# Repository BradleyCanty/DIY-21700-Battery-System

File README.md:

# DIY-21700-Battery-System
## Introduction
This is a do-it-yourself battery system intended for use with Unmanned Aerial Vehicles or Unmanned Ground Vehicles.

It consists of...

1) a battery using lithium ion 21700-form-factor cells, with battery configurations spanning from 6s3p to 12s6p
2) a vehicle adapter with place-to-lock/press-to-unlock latching mechanism
3) an off-vehicle charging station

(12s4p battery system configuration shown below)

**This is a complete and working system, with all design files (CAD and PCB design) provided for your use:**\
Multiple battery system configurations have been built and flight tested. Additionally, all CAD models have been 3D printed to ensure they work as intended. Finally, if none of the configurations presented here suit your needs then you can create your own battery configuration, since all CAD files (Solidworks part files and STLs) and PCB design files (KiCad project files) are included here for your use.

**Version 2 will have cell voltage and temperature monitoring safety features (sent as a BATTERY_STATUS message over MAVLink to MAVLink-compatible autopilot software, such as ArduPilot and PX4) so star this repo for updates**

## Purpose
The parametric nature of this system allows designing and building a battery system specific to your vehicle's requirements. As such, **the value add of this system is threefold:**
1) you can use cells of your choice (i.e., can optimize for either power output or energy capacity) in a configuration suitable for your vehicle's operating envelope
2) you can enjoy a significant cost savings (~50% discount at the time of this writing) by building it yourself (see 'Bill of Materials' section for cost info)
3) the battery's latching mechanism presents a common interface for battery swapping (either manually or by robot arm); this is important since battery swapping vastly increases system uptime when compared with on-board charging

## Battery Mounting Choice
This battery system is designed such that the battery itself is top-mounted onto the vehicle its powering (and top-mounted onto its charging station). This mounting method was chosen to simplify battery swapping (either by human hand or by robot gripper); the process to swap the battery is as follows:
1. get within close proximity of the battery
2. translate grippers directly over the battery
3. rotate grippers to be aligned with the battery end plates
4. translate grippers underneath each end plate ledge
5. close grippers such that the end plate buttons are pressed down, thus unlatching the battery from the vehicle adapter
6. lift battery away from the vehicle
7. carry battery to its charging station

A similar but reversed process occurs for taking a fully charged battery off its charging station to the vehicle.

If you intend for such a battery to power your multirotor you might ask: "wouldn't the multirotor be top heavy, thereby adversely affecting stability and control?". The simple answer is no, it wouldn't **if you mount the battery directly above the bulkhead where the motor arms are mounted to the body**. In doing this, the center of gravity moves closer to the thrust plane (i.e. the plane where the rotors spin), which decreases overall inertia and thereby increases control responsiveness. So the overall impact is positive, not adverse. As final proof of functionality, I have personally flight tested a multirotor using a 12s4p battery, with no stability or control issues whatsoever.

(12s4p battery and vehicle adapter used on large quadcopter shown below)

Details on mounting the vehicle adapter to the vehicle can be found in Build Step 7: [Integrate vehicle adapter into vehicle](5_Integration_and_Test_Instructions/1_Vehicle_Adapter_Integration_Instructions/vehicle_adapter_integration_instructions.md)

## Cell Form Factor Choice
Considering the cell form factor, **21700 cells** (i.e. cylindrical cells having 21[mm] height and 70[mm] length) **are used in the battery since they are cheap, easily obtained, and have high gravimetric energy density**. In comparison to other cells types, 18650 cells tend to have lower gravimetric energy density, while 4680 cells, prismatic cells, and pouch cells aren't widely available to the general public (as of late 2026). Concerning battery design, the battery configuration is defined by its number of cells in series (which sets its voltage) and its number of cells in parallel (which sets its charge capacity and its max current draw limit). In the system presented here, the possible number of cells in series ranges from 6 to 12, while the possible number of cells in parallel ranges from 3 to 6. That is, the smallest possible battery configuration is one having 6 cells in series and 3 cells in parallel (18 cells total), while the largest battery configuration is one having 12 cells in series and 6 cells in parallel (72 cells total).

(6s3p and 12s6p battery system configurations shown below)

As a final note, **the cell-to-pack mass fraction across all battery configurations is found to be around 83%**. This value is important since once you select a specific 21700 cell to use, you can then estimate the battery's total mass and the battery's gravimetric energy density:\
$m_{battery} \approx m_{cell} * M * N / CPMF$ = battery mass [kg]\
where\
$m_{cell}$ = cell mass [kg]\
$M$ = number of cells in series\
$N$ = number of cells in parallel\
$CPMF$ = cell-to-pack mass fraction

$E_{battery}^* = (battery\ nominal\ voltage) * (battery\ charge\ capacity)$\
&nbsp; &nbsp; &nbsp; &nbsp; &nbsp; &nbsp; &thinsp;= $(M * V_{cell, nominal})*(N * Q_{cell,expected}) / m_{battery}$\
&nbsp; &nbsp; &nbsp; &nbsp; &nbsp; &nbsp; &thinsp;= gravimetric energy density [Wh/kg]\
where\
$V_{cell, nominal}$ = nominal cell voltage = 3.6[V] (for li-ion cell)\
$Q_{cell,expected}$ = expected cell charge capacity for normal vehicle operation (computed using the process outlined in 'Steps for Selecting a Battery Configuration' section found below)

For example, for a battery having 8 cells in series and 5 cells in parallel (i.e. MsNp = 8s5p) using EVE 50PL 21700 cells, we have\
$m_{cell} = 0.066 [kg]$ (real-world value... datasheet gives 0.072 [kg] per cell)\
$M$ = 8\
$N$ = 5\
$CPMF$ = 0.83\
$Q_{cell,expected}$ = 4.5 [Ah]

Then, battery mass and gravimetric energy density are computed to be\
$m_{battery} \approx 0.066 * 8 * 5 / 0.083 =  3.18$ [kg]\
$E_{battery}^* = (8 * 3.6)*(5 * 4.5) / 3.18$ = 203.8 [Wh/kg]

## Safety
Additionally, safety is paramount. A temperature sensor circuit consisting of a microcontroller and busbar voltage sensing is in progress (I had assumed thermistors would work in the cell failure detection role, but apparently the thermal mass of the busbar is too large to detect it in time). I am in the process of designing and prototyping a circuit which detects voltages at each busbar and sends them in MAVLink packets over UART to the flight controller (running either Ardupilot or PX4), with options of alerting the pilot or autolanding the vehicle if a measured busbar voltage is lower than some threshold. **The software development, physical packaging, and testing have posed significant issues which require a non-trivial amount of iteration, time, and money: I am working through these issues, but at some point I need to call a "pencils down" and declare victory, so Version 1 is without this safety feature. However, I assure you that Version 2 will have this safety feature, so stay tuned for that.** Additionally, I am in the process of making a low voltage alarm circuit featuring a buzzer and orange LED lights which buzz and flash upon low voltage detection, which I intend to include in Version 2 of this project.

Concerning the electrical system limitations, the PCBs (the 'Battery Board', 'Vehicle Adapter', and 'Antispark Board') are designed to handle 60 amps of continuous current (assuming a maximum temperature rise of 20°C). **You should consider the 60 amps of continuous current limitation as the primary limiting factor in your selected configuration.** This current limitation is written out on each PCB via silkscreen text. Note that this is max continuous current, <ins>not max short-duration current</ins>: max short-duration current is dictated by the 21700 cell you choose (should be listed in its datasheet) and the number of cells used in parallel. Specifically, its given by:

$I_{max\ total,short\ duration}$ = $I_{max\ cell} * N$\
where\
$N$ = number of cells in parallel

## DIY or Build from a Kit
Building this system consists of many steps (see 'Build Steps' section), and requires specific tools (see 'Required Tools' section). As a consequence, many people may find that doing this on their own is too advanced for them. Therefore, a kit is available to make the the build process easier: in essence, all you need to do upon receiving the kit is
1) Insert your favorite cells (purchased separately) into the fully-prepared 3D printed frames
2) spot weld the busbars to the cell terminals
3) Solder the balance cable wires to the busbars
4) Cut and solder the 8 AWG power wires to the battery PCB
5) fasten the fully-prepared 3D printed parts and pre-populated PCBs together with screws
6) Test the battery by performing a few charge/discharge cycles on your battery charger (the battery charger is not included in the kit)

Then, the tools required for building the battery system from the kit is
1) a suitable spot welder
2) soldering iron
3) metric hex wrenches
4) a suitable battery charger

Kit contents, pricing, and ordering information can be found [here](0_Misc/build_kit_info.md).

Whether you are building from raw materials or building from the kit, the 'Build Steps' section found below contains pictures and descriptions at each step to aid in the build process.

## Battery System Components in Detail
The battery system consists of the following components:
1) the battery
2) the vehicle adapter
3) the charging station

Each is explained in turn

### The Battery
Each component is sized according to the chosen battery configuration. Possible battery configurations range from 6 to 12 cells in series, and 3 to 6 cells in parallel. Spelled out, these configurations are:
* Six in series:
    - Three in parallel (6s3p)
    - Four in parallel (6s4p)
    - Five in parallel (6s5p)
    - Six in parallel (6s6p)
* Eight in series:
    - Three in parallel (8s3p)
    - Four in parallel (8s4p)
    - Five in parallel (8s5p)
    - Six in parallel (8s6p)
* Ten in series:
    - Three in parallel (10s3p)
    - Four in parallel (10s4p)
    - Five in parallel (10s5p)
    - Six in parallel (10s6p)
* Twelve in series:
    - Three in parallel (12s3p)
    - Four in parallel (12s4p)
    - Five in parallel (12s5p)
    - Six in parallel (12s6p)
  
  The battery consists of
  - two frames, which hold the cells between them

  - a top plate, which covers the top frame

  - a bottom plate, which connects with the bottom frame and houses the female 12-pin power and balance connectors
    <p align="center">

    </p>
    
  - two end plates, which clamp the frames together and serve as handles containing the button-press-to-unlatch mechanism

### The Vehicle Adapter
Connects the battery with the vehicle, both mechanically and electrically. For the mechanical interface, it has two latches which interface with the two button-press-to-unlatch mechanisms on either end of the battery. For the electrical interface, it has a male 12-pin connector.

### The Charging Station
Interfaces the battery with a standard RC battery charger via XT60 connector for power and JST-XH connector for balancing. Again, <ins>this is not a charger itself: its an interface between the battery and the charger</ins>.

## Steps for Selecting a Battery Configuration
In general,\
**The number of cells in series determines the battery voltage:**\
$battery\ max\ voltage = (cell\ max\ voltage) * (number\ of\ cells\ in\ series)$\
where\
$cell\ max\ voltage$ = 4.1 V (for LiIon cells)

**The number of cells in parallel determines the battery charge capacity:**\
$$battery\ charge\ capacity = (cell\ expected\ charge\ capacity) * (number\ of\ cells\ in\ parallel)$$\
where\
$cell\ expected\ charge\ capacity$ = a function of expected average current draw in cruise (fixed wing) or hover (VTOL)

Specifically, to find the battery's expected charge capacity, check the 21700 cell's datasheet for the plot of Voltage vs Charge Capacity (which contains curves of various discharge rates) and then match your vehicle's expected average current draw divided by the number of cells in parallel to the corresponding discharge rate curve in the plot. Finally, find the cell's capacity corresponding to an "empty" voltage of around 2.8 V, and then multiply it by the number of cells in parallel to get the battery's charge capacity.

For example, suppose you are using Molicel P50B cells in an 8s5p battery configuration on a vehicle expected to draw 1300 Watts of power in nominal operation, then the steps to find the expected charge capacity are as follows: 

1) Compute the average discharge current in nominal operation:\
   $I_{avg}$ = $P_{nominal}$ / $V_{batt,nominal}$ = $P_{nominal}$ / ($V_{cell,nominal}$ * M)\
   where\
   M = number of cells in series = 8\
   $V_{cell,nominal}$ = li-ion cell nominal voltage = 3.6V
   
   Plugging in the values...\
   $I_{avg}$ = 1300 / (3.6 * 8) = 45.1 Amps
   
2) Compute the discharge rate per cell: 45.1 Amps / 5 cells in parallel = 9.03 Amps
3) Find the Voltage vs Charge capacity plot in the Molicel P50B datasheet
4) On the plot, draw a horizontal line at the cutoff voltage (here 2.8V) across the plot, and stop upon reaching the curve corresponding to the cell's discharge rate (here the 10 Amp curve)
5) On the plot, draw a vertical line to the abscissa to obtain the cell's nominal charge capacity
(see plot below)

6) Finally, compute the battery's nominal charge capacity:\
   $Q_{batt,nominal}$ = $Q_{cell,nominal}$ * M\
   where\
   M = number of cells in parallel = 5

   Plugging in the values...\
   $Q_{batt,nominal}$ = 4500 * 5 = 22500 mAh = 22.5 Ah

Once battery nominal charge capacity is found, you can **compute the vehicle's expected endurance** (i.e. operating time under nominal conditions) using the following equation:\
t = $V_{batt,nominal}$ * $Q_{batt,nominal}$ / P\
where\
$V_{batt,nominal}$ = $V_{cell,nominal}$ * M

Using the values from the previous example, we have...\
t = (3.6 * 8) * 22.5 / 1300 = 0.498 hours = 29.9 minutes

This is all predicated on the accuracy of your predicted power draw, which is a function of your payload mass, battery mass, structure mass, and the type of motors (and, for multirotors, the size of the rotors) used on the vehicle. **So, in summary, selecting a battery configuration is an iterative process.**

For a multirotor, the appropriate battery configuration can be determined using this [multirotor design methodology](0_Misc/multirotor_design_methodology.md).

## Required Tools
* Soldering iron (for general soldering)
* Threaded insert soldering iron tip 
* Hot plate (for SMD soldering)
* Spot welder (for battery bus bar welding)
* 3D printer
* Deburr tool (for removing edge artifacts from 3D prints)
* Wire stripper
* Wire cutter
* Super glue
* Sheet metal shears (for cutting busbars)
* Hand drill or drill press (for cutting wire pass-through holes into busbars)

## Bill of Materials (BOM)
The battery BOM is found [here](3_Bill_of_Materials/battery_bom.md)

The vehicle adapter BOM is found [here](3_Bill_of_Materials/vehicle_adapter_bom.md)

The charging station BOM is found [here](3_Bill_of_Materials/charging_station_bom.md)

## Build Steps
### Things you should know before starting:
* ASA filament is used in all the 3D printed parts since it's ultraviolet resistant, so it can be left outdoors without degrading in strength. However, 3D printing it releases toxic fumes (specifically, printing it releases volatile organic compounds along with ultrafine particles, either of which may be carcinogenic), so use a fan-filter system when printing ASA. Also, ASA is prone to warping and so must be printed in a heated enclosure. Even with a heated enclosure, a brim is often needed on large parts to keep them from peeling away from the print bed. If the peeling at edges occurs at any time during the print, its a failed print so cancel it and reprint it with a 5 mm increase to the brim width. Do this iteratively until the print is successful.
* The printed circuit boards (PCBs) can be manufactured by uploading the zipped gerber files (provided in the repo) to a PCB manufacturer, such as PCBWay or JLCPCB
* The PCB components can be purchased from electronic component suppliers, such as DigiKey or Mouser, but know that you will need to hand-solder the through-hole components and hot plate solder the SMD components
* The build process is very frustrating and time-consuming, especially
    - 3D printing the parts, with ASA prints likely to fail due to warping
    - populating the antispark circuits with SMD components and soldering them using a hot plate
    - cutting wires to length and soldering them
    
    To save time and frustration, pre-made kits for each battery configuration are available for purchase: see 'DIY or Build from a Kit' section above for details on ordering a kit.

### To make the build process as simple as possible, proceed in this order:
  1. **Decide on a battery configuration**
  2. **Order the required PCBs and associated components:**\
     each system needs two antispark PCBs, one charging station PCB (pick the one that matches your configuration), one battery PCB (pick the one that matches your configuration), and one vehicle adapter PCB, all found [here](2_PCB_Files). See the READMEs for BOMs and ordering information.
     
  4. **Build the antispark boards:** instructions found [here](4_Build_Instructions/1_Antispark_Build_Instructions/antispark_build_instructions.md)
  5. **Build the charging station:** instructions found [here](4_Build_Instructions/2_Charging_Station_Build_Instructions/charging_station_build_instructions.md)
  7. **Build the battery:** instructions found [here](4_Build_Instructions/3_Battery_Build_Instructions/battery_build_instructions.md)
  8. **Build the vehicle adapter:** instructions found [here](4_Build_Instructions/4_Vehicle_Adapter_Build_Instructions/vehicle_adapter_build_instructions.md)
  9. **Integrate vehicle adapter into vehicle:** instructions found [here](5_Integration_and_Test_Instructions/1_Vehicle_Adapter_Integration_Instructions/vehicle_adapter_integration_instructions.md)
  10. **Perform vehicle operating envelope testing:** instructions found [here](5_Integration_and_Test_Instructions/2_Vehicle_Envelope_Testing_Instructions/vehicle_envelope_testing_instructions.md)

## TO DO
### V1 TO DO IMMEDIATELY
* Consolidate and simplify the battery sizing methodology

### V1 TO DO LATER
* Take pictures of antispark circuit build and put into instructions
* Complete the 'Perform vehicle operating envelope testing' instructions

### V2 TO DO IMMEDIATELY
* Replace JST-XH balance connectors used in battery interface with machine header pins: female on battery, male on vehicle adapter and charging station
* Implement safety features: measure voltages at each busbar, and measure temperatures at two cells, and report as a BATTERY_STATUS message over MAVLink
* Refactor end plate latching mechanism to have clamp-from-top-to-unlatch, replacing the button-press-to-unlatch. This makes the battery usable on fixed-wing platforms, since battery swapping operations interact with the top surface only, as opposed to V1 where side clasping is required. It will also probably make it easier to automate battery swapping via robot arm, due to the simplified interface.

### V2 TO DO LATER
* Replace balance wires with a BMS
* Extend battery configurations to 24s12p

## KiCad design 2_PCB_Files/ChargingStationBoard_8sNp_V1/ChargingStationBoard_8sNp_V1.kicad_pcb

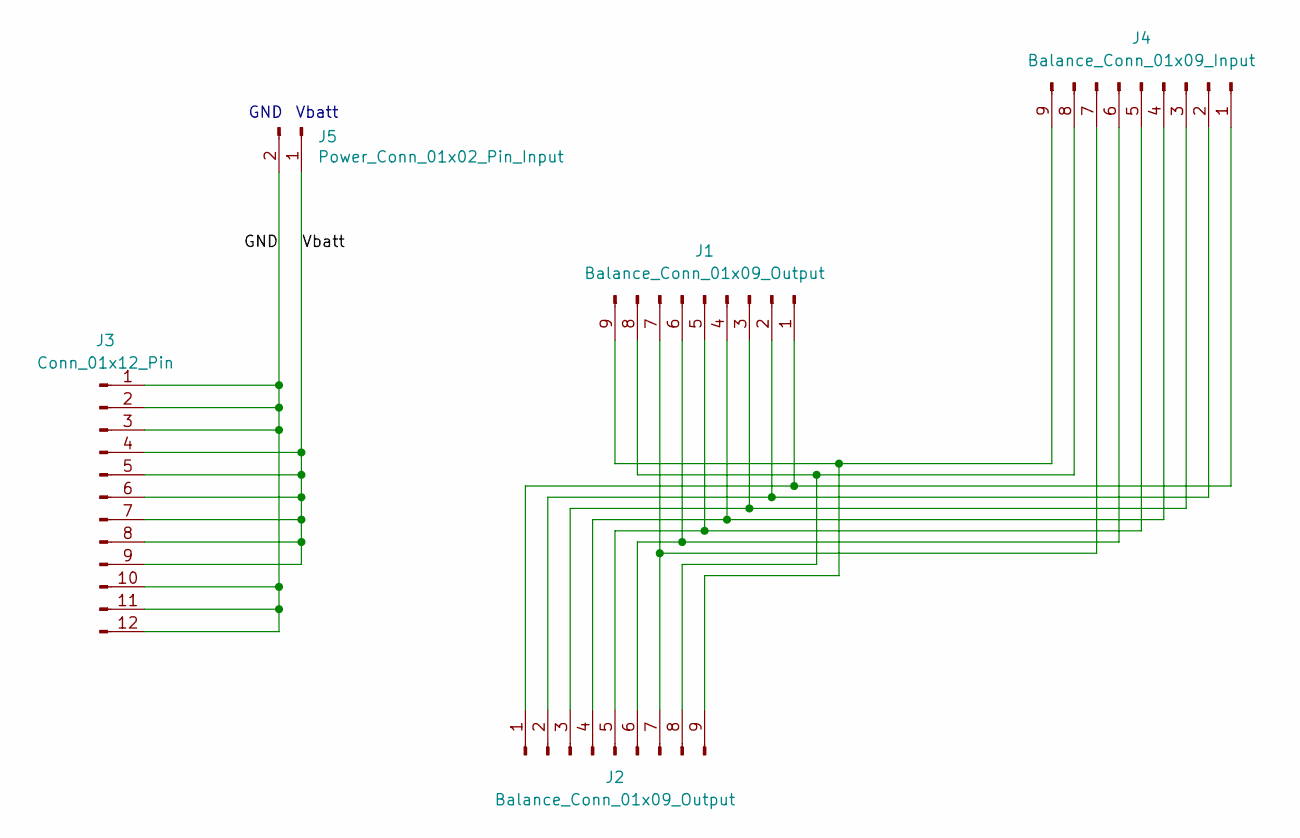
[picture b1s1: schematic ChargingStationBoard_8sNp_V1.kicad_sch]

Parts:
J1, J2: Balance_Conn_01x09_Output; JST_XH_B9B-XH-A_1x09_P2.50mm_Vertical
J3: Conn_01x12_Pin; MISTA_MSD-DB01M
J4: Balance_Conn_01x09_Input; misc_pads_9_pin_1.75mmx1.75mm
J5: Power_Conn_01x02_Pin_Input; power_pads_2_pins_8mmx8mm

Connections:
/GND: J3.1, J3.2, J3.3, J3.10, J3.11, J3.12, J5.2
/Vbatt: J3.4, J3.5, J3.6, J3.7, J3.8, J3.9, J5.1
unnamed: J1.1, J2.1, J4.1
unnamed: J1.2, J2.2, J4.2
unnamed: J1.3, J2.3, J4.3
unnamed: J1.4, J2.4, J4.4
unnamed: J1.5, J2.5, J4.5
unnamed: J1.6, J2.6, J4.6
unnamed: J1.7, J2.7, J4.7
unnamed: J1.8, J2.8, J4.8
unnamed: J1.9, J2.9, J4.9

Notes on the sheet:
GND
Vbatt

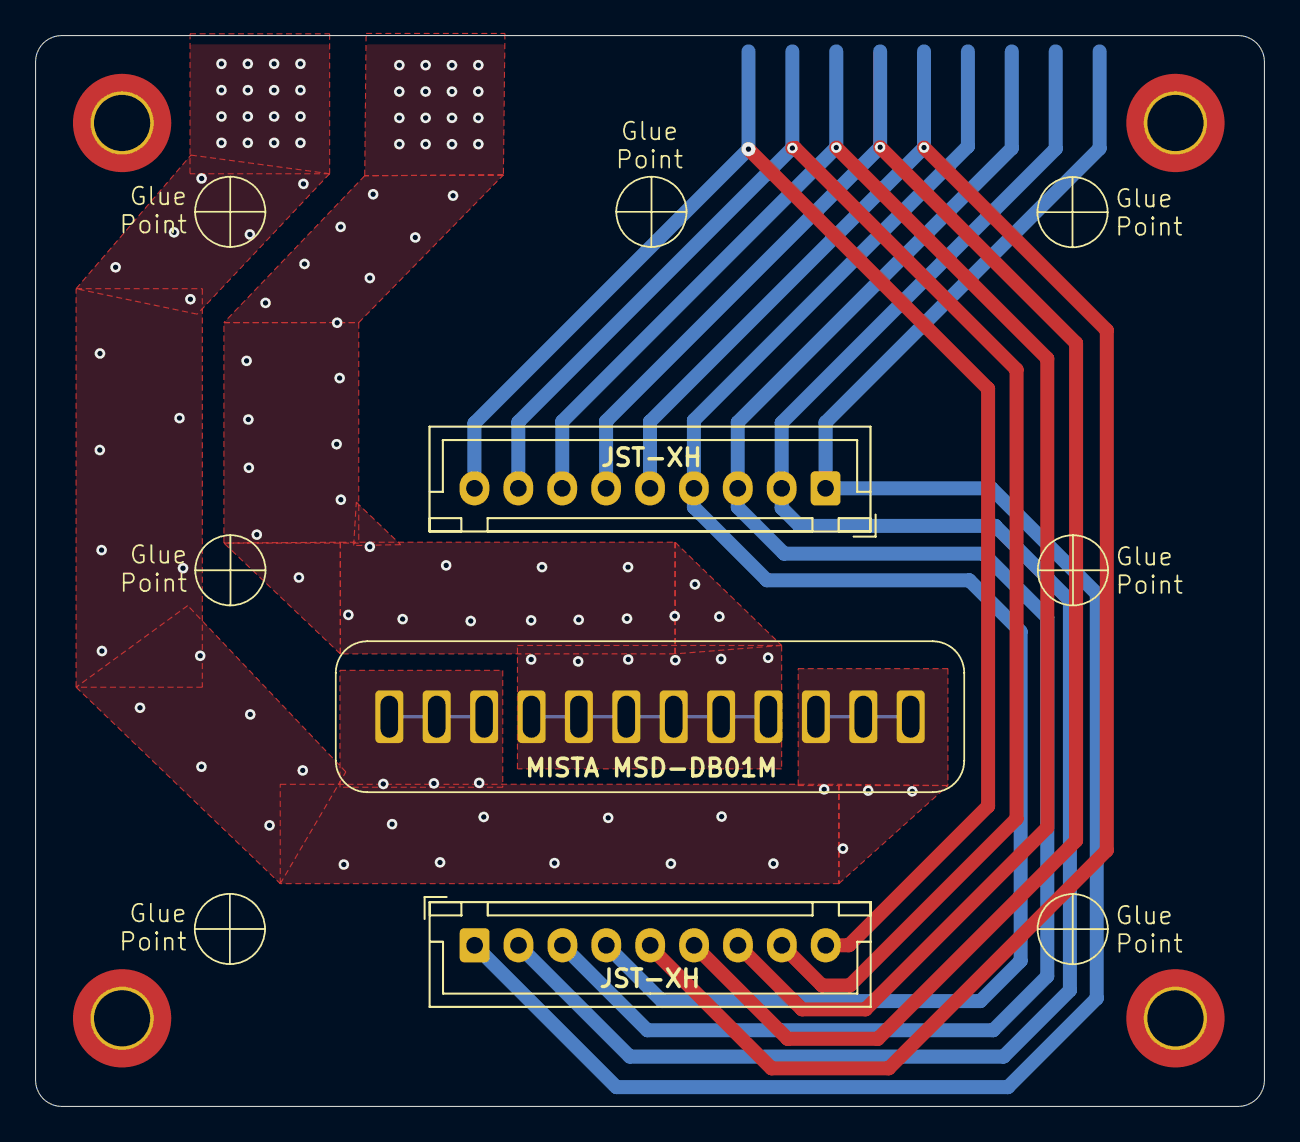
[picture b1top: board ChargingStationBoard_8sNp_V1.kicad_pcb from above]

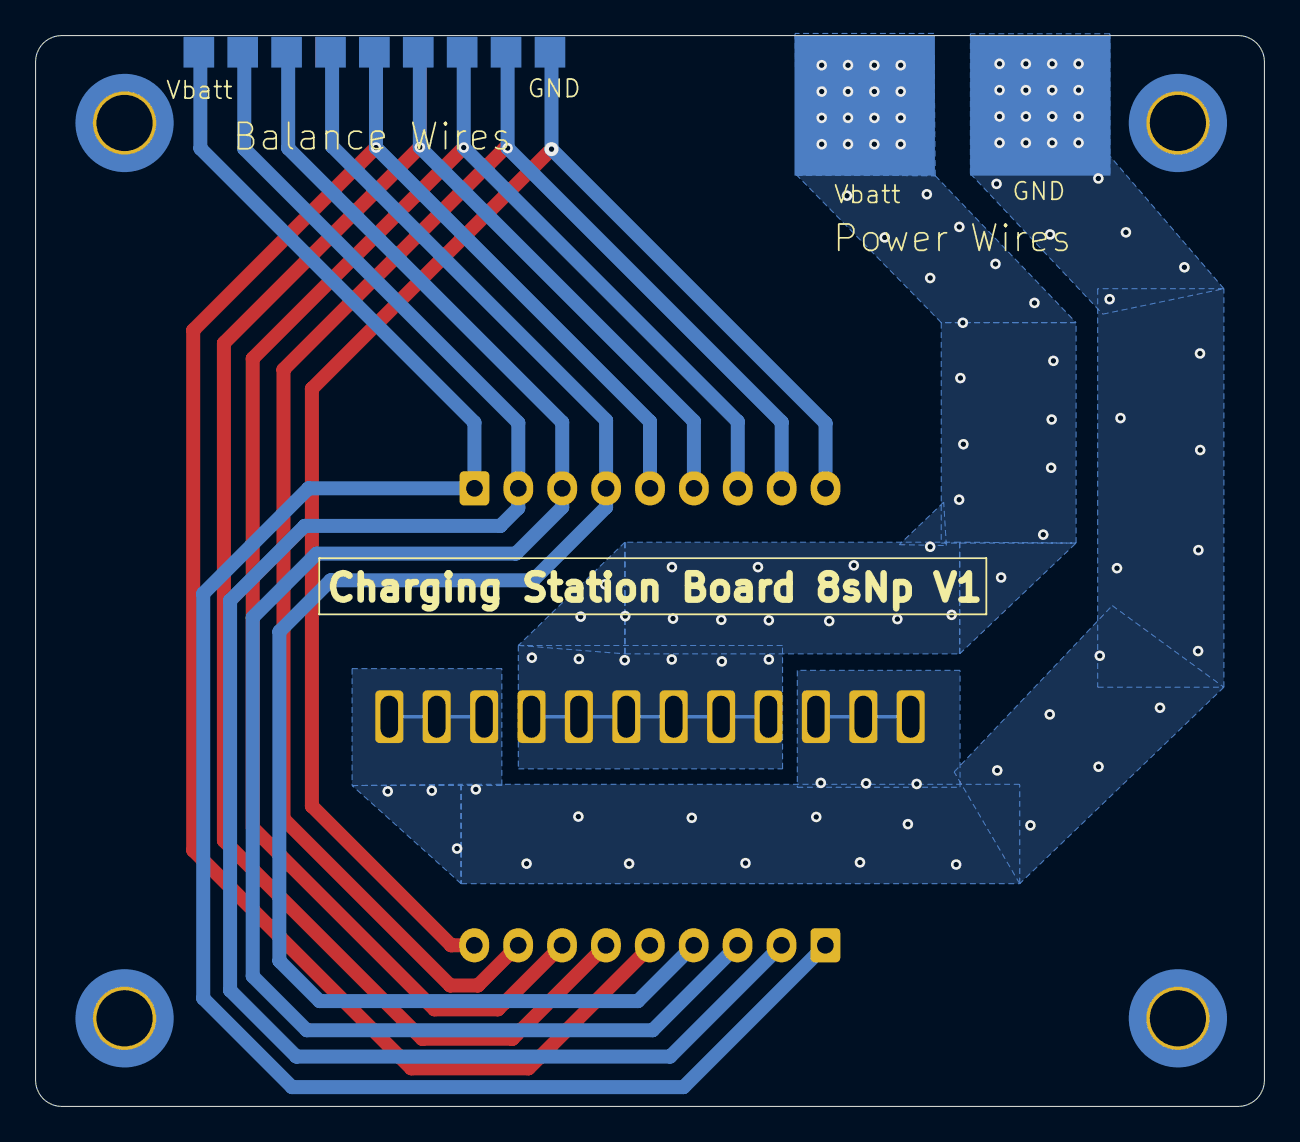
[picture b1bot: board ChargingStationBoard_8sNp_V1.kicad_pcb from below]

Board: 4 copper layers, 70.0 x 61.0 mm, 5 parts (2 on the bottom side), 11 nets.

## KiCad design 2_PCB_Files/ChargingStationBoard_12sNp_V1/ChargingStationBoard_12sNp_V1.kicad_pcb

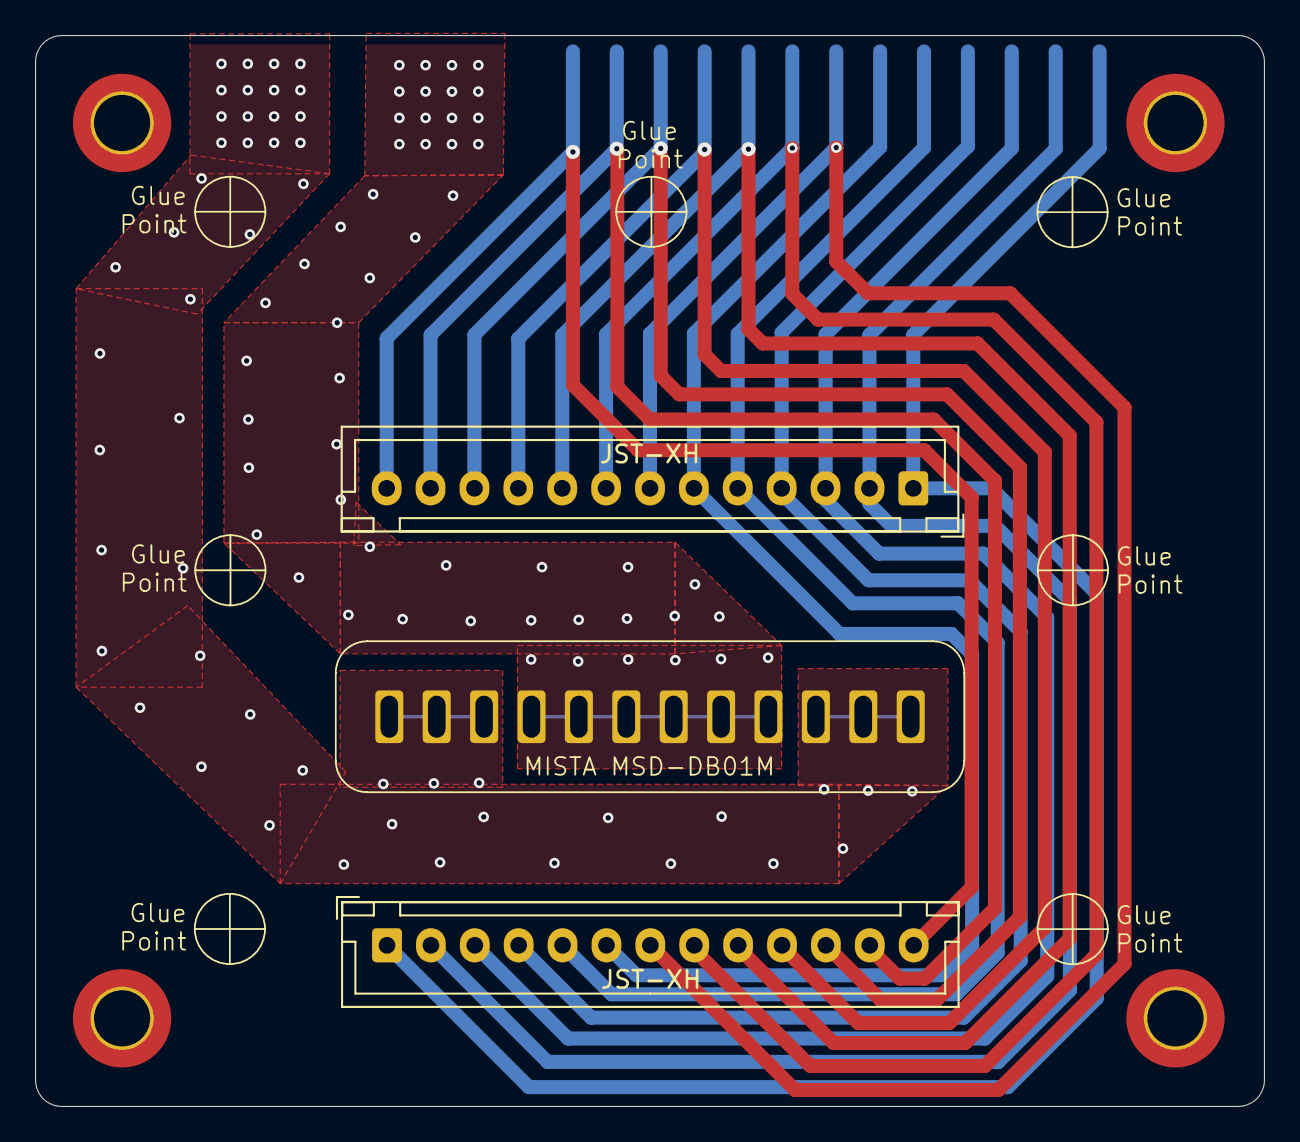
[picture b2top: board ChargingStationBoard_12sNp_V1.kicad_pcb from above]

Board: 4 copper layers, 70.0 x 61.0 mm, 5 parts (1 on the bottom side), 15 nets.

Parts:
J4: Balance_Conn_01x13_Pin_Input; balance_pads_13_pin
J5: Power_Conn_01x02_Pin_Input; power_pads_2_pins
JST-XH: Balance_Conn_01x13_Output; JST_XH_B13B-XH-A_1x13_P2.50mm_Vertical
JST-XH#2: Balance_Conn_01x13_Pin_Output; JST_XH_B13B-XH-A_1x13_P2.50mm_Vertical
MISTA MSD-DB01M: Conn_01x12_Pin; MISTA_MSD-DB01

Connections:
/GND: J5.2, MISTA MSD-DB01M.1, MISTA MSD-DB01M.2, MISTA MSD-DB01M.3, MISTA MSD-DB01M.10, MISTA MSD-DB01M.11, MISTA MSD-DB01M.12
/Vbatt: J5.1, MISTA MSD-DB01M.4, MISTA MSD-DB01M.5, MISTA MSD-DB01M.6, MISTA MSD-DB01M.7, MISTA MSD-DB01M.8, MISTA MSD-DB01M.9
unnamed: J4.1, JST-XH.1, JST-XH#2.1
unnamed: J4.2, JST-XH.2, JST-XH#2.2
unnamed: J4.3, JST-XH.3, JST-XH#2.3
unnamed: J4.4, JST-XH.4, JST-XH#2.4
unnamed: J4.5, JST-XH.5, JST-XH#2.5
unnamed: J4.6, JST-XH.6, JST-XH#2.6
unnamed: J4.7, JST-XH.7, JST-XH#2.7
unnamed: J4.8, JST-XH.8, JST-XH#2.8
unnamed: J4.9, JST-XH.9, JST-XH#2.9
unnamed: J4.10, JST-XH.10, JST-XH#2.10
unnamed: J4.11, JST-XH.11, JST-XH#2.11
unnamed: J4.12, JST-XH.12, JST-XH#2.12
unnamed: J4.13, JST-XH.13, JST-XH#2.13

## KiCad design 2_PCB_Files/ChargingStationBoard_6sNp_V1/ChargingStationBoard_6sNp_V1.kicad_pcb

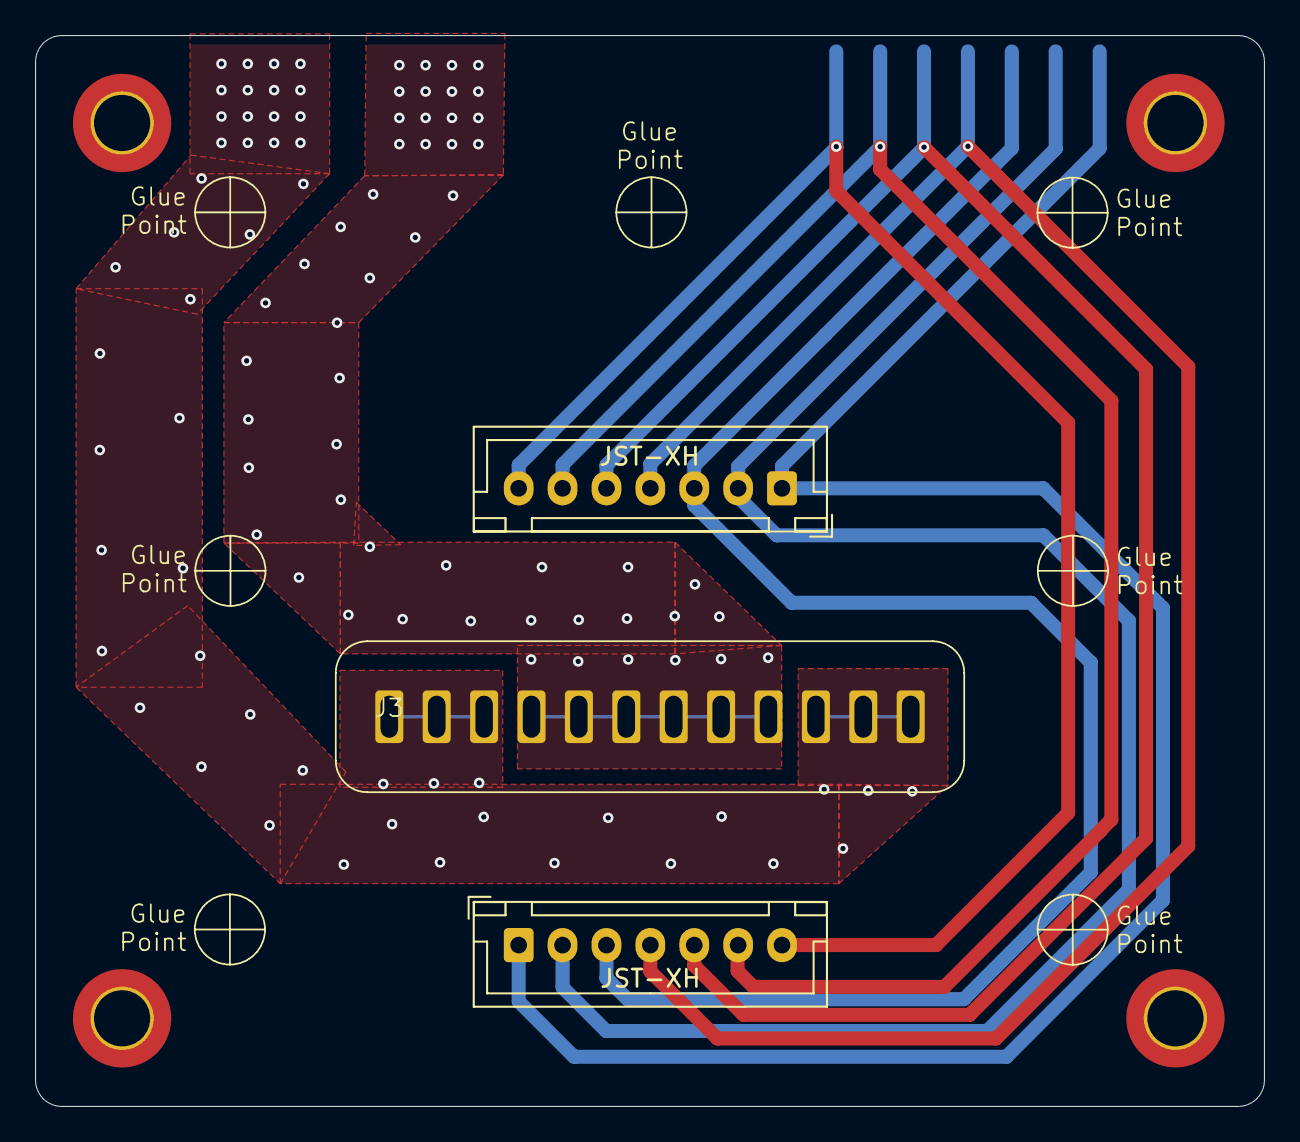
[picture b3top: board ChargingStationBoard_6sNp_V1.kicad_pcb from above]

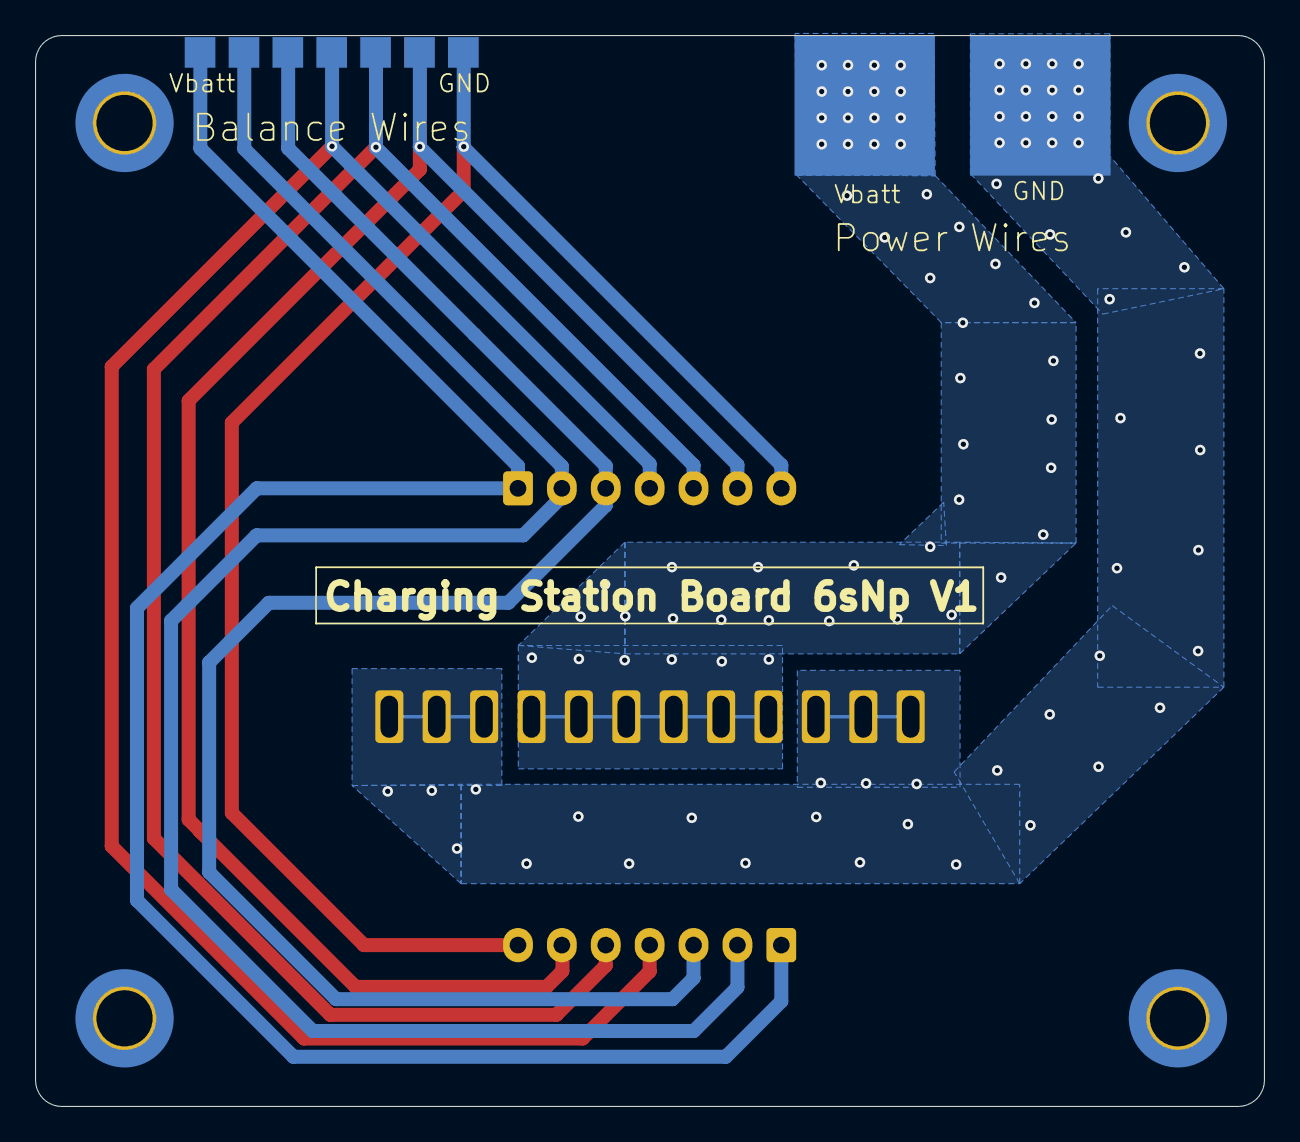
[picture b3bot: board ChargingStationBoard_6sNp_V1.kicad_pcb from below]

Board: 4 copper layers, 70.0 x 61.0 mm, 5 parts (2 on the bottom side), 9 nets.

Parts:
J1: Conn_01x07_Pin_Input; misc_pads_7_pin_1.75mmx1.75mm
J3: Conn_01x12_Pin; MISTA_MSD-DB01M
J5: Power_Conn_01x02_Pin_Input; power_pads_2_pins_8mmx8mm
JST-XH: Conn_01x07_Pin_Output; JST_XH_B7B-XH-A_1x07_P2.50mm_Vertical
JST-XH#2: Conn_01x07_Pin_Output; JST_XH_B7B-XH-A_1x07_P2.50mm_Vertical

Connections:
/GND: J3.1, J3.2, J3.3, J3.10, J3.11, J3.12, J5.2
/Vbatt: J3.4, J3.5, J3.6, J3.7, J3.8, J3.9, J5.1
unnamed: J1.1, JST-XH.1, JST-XH#2.1
unnamed: J1.2, JST-XH.2, JST-XH#2.2
unnamed: J1.3, JST-XH.3, JST-XH#2.3
unnamed: J1.4, JST-XH.4, JST-XH#2.4
unnamed: J1.5, JST-XH.5, JST-XH#2.5
unnamed: J1.6, JST-XH.6, JST-XH#2.6
unnamed: J1.7, JST-XH.7, JST-XH#2.7

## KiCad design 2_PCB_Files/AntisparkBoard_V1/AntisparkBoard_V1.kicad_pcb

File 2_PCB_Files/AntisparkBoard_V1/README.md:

## KiCad 3D View
Below are the screenshots of this board from KiCad's 3D board viewer.

## BOM
| References | Value | Footprint | Quantity |
| --- | --- | --- | --- |
| C1 | 4.7 μF | C_0805_2012Metric | 1 |
| R1, R2, R4, R5 | 1 MΩ | R_0603_1608Metric | 4 |
| R3 | 4.7 Ω | R_Axial_DIN0414_L11.9mm_D4.5mm_P15.24mm_Horizontal | 1 |
| R6 | 100 kΩ | R_0603_1608Metric | 1 |
| R7 | 100 Ω | R_0603_1608Metric | 1 |
| D1, D2 | 12 V | D_MiniMELF | 2 |
| D3 | Zener 0.5 V | D_SOD-123 | 1 |
| D4 | 10 V | D_SOD-323 | 1 |
| Q1, Q2 | IRFS7530TRL7PP | IRFS7530TRL7PP | 2 |
| Q3 | FDS5670 | SOIC127P600X175-8N | 1 |
| Q4 | NTA4001NT1G | SOT50P160X90-3N | 1 |

## How to Purchase the Board and Components
To purchase PCBs, take the zipped 'fab' directory (which contains PCB manufacturing instructions) and upload it to a PCB manufacturer's website (e.g. [JLCPCB](https://JLCPCB.com) or [PCBWay](https://PCBWay.com))

To purchase components, I recommend [Digikey](https://digikey.com) or [Mouser](https://mouser.com)

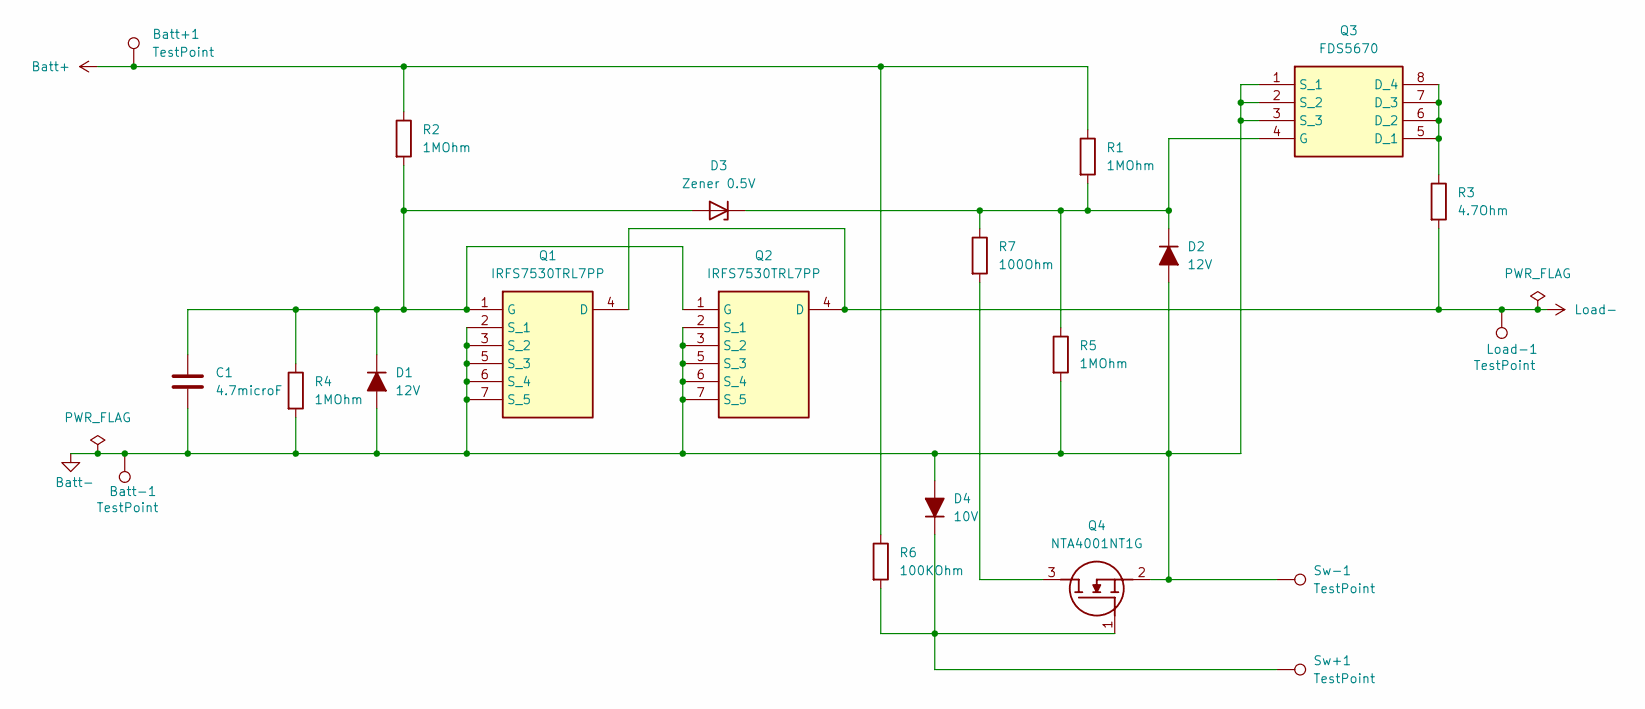
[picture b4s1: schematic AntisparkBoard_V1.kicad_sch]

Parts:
Batt+1: TestPoint; TestPoint_Pad_D2.0mm
Batt-1: TestPoint; pad_6mmx6mm
C1: 4.7microF; C_0805_2012Metric
D1, D2: 12V; D_MiniMELF
D3: Zener 0.5V; D_SOD-123
D4: 10V; D_SOD-323
Load-1: TestPoint; pad_6mmx6mm
Q1, Q2: IRFS7530TRL7PP; Manufacturer_Part_Number IRFS7530TRL7PP; Mouser Part Number 942-IRFS7530TRL7PP
Q3: FDS5670; SOIC127P600X175-8N; Manufacturer_Part_Number FDS5670; Mouser Part Number 512-FDS5670
Q4: NTA4001NT1G; SOT50P160X90-3N; Manufacturer_Part_Number NTA4001NT1G; Mouser Part Number 863-NTA4001NT1G
R1, R2, R4, R5: 1MOhm; R_0603_1608Metric
R3: 4.7Ohm; R_Axial_DIN0414_L11.9mm_D4.5mm_P15.24mm_Horizontal
R6: 100KOhm; R_0603_1608Metric
R7: 100Ohm; R_0603_1608Metric
Sw+1: TestPoint; TestPoint_Pad_D2.0mm
Sw-1: TestPoint; TestPoint_Pad_D2.0mm

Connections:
Batt+: Batt+1.1, R1.1, R2.1, R6.1
Batt-: Batt-1.1, C1.2, D1.2 (A), D2.2 (A), D4.2 (A), Q1.2 (S_1), Q1.3 (S_2), Q1.5 (S_3), Q1.6 (S_4), Q1.7 (S_5), Q2.2 (S_1), Q2.3 (S_2), Q2.5 (S_3), Q2.6 (S_4), Q2.7 (S_5), Q3.1 (S_1), Q3.2 (S_2), Q3.3 (S_3), Q4.2 (S), R4.2, R5.2, Sw-1.1
Load-: Load-1.1, Q1.4 (D), Q2.4 (D), R3.2
unnamed: C1.1, D1.1 (K), D3.2 (A), Q1.1 (G), Q2.1 (G), R2.2, R4.1
unnamed: D2.1 (K), D3.1 (K), Q3.4 (G), R1.2, R5.1, R7.1
unnamed: D4.1 (K), Q4.1 (G), R6.2, Sw+1.1
unnamed: Q3.5 (D_1), Q3.6 (D_2), Q3.7 (D_3), Q3.8 (D_4), R3.1
unnamed: Q4.3 (D), R7.2

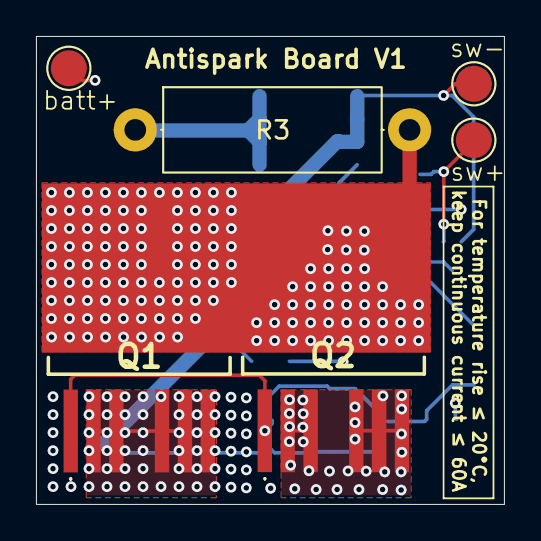
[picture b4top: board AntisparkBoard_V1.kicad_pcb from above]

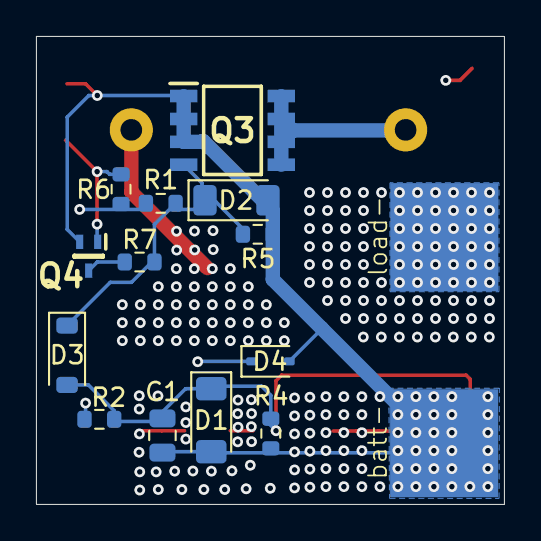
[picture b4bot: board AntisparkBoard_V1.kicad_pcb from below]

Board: 8 copper layers, 26.0 x 26.0 mm, 21 parts (15 on the bottom side), 8 nets.

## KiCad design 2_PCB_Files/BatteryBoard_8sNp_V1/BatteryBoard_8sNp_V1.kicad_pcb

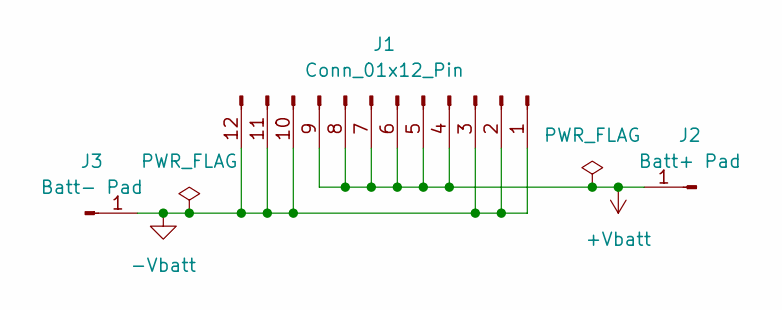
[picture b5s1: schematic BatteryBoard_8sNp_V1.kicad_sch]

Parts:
J1: Conn_01x12_Pin; MISTA_MSD-DB01F
J2: Batt+ Pad; pad_10p5mmx6mm
J3: Batt- Pad; pad_10p5mmx6mm

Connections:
+Vbatt: J1.4, J1.5, J1.6, J1.7, J1.8, J1.9, J2.1
-Vbatt: J1.1, J1.2, J1.3, J1.10, J1.11, J1.12, J3.1

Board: 6 copper layers, 3 parts (3 on the bottom side), 2 nets, no tracks yet.
